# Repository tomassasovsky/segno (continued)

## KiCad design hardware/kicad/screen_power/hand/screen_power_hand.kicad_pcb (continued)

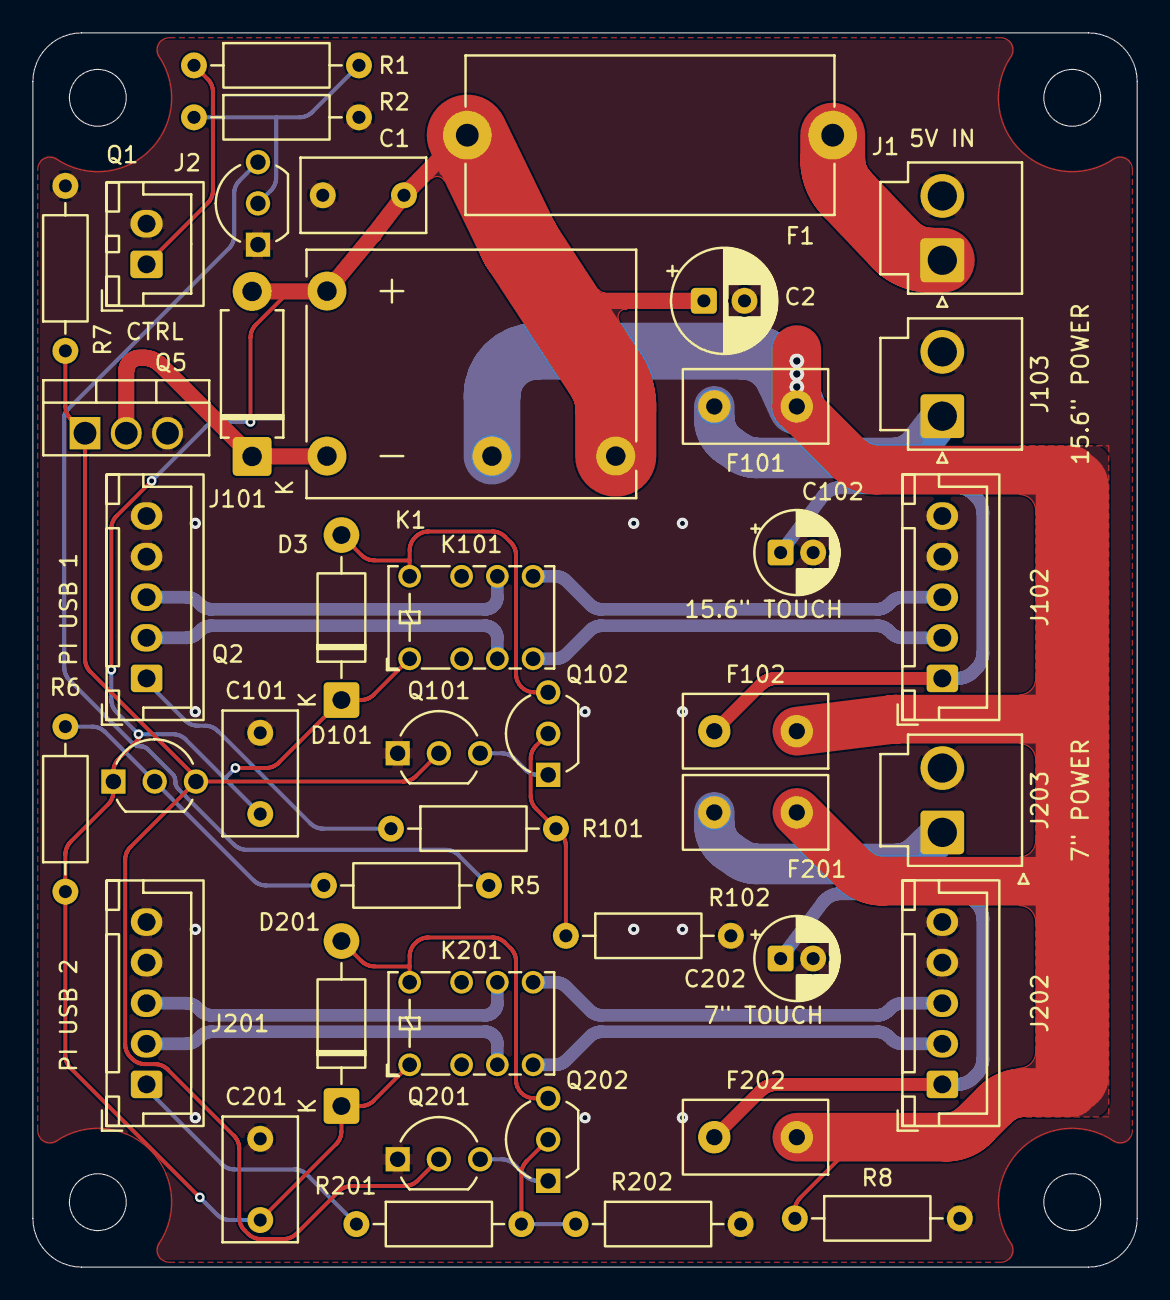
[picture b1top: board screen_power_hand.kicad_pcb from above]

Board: 2 copper layers, 68.0 x 76.0 mm, 46 parts (0 on the bottom side), 30 nets.

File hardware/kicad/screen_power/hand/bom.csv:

ref,value,footprint,mpn,group,quantity
J1,AUX 5V INPUT,Connector_JST:JST_VH_B2P-VH_1x02_P3.96mm_Vertical,B2P-VH(LF)(SN),Control,1
F1,8A time-lag,screen_power:Fuseholder_Schurter_OGN_0031.8201,0001.2513,Control,1
J2,GPIO17 / GND,Connector_JST:JST_XH_B2B-XH-A_1x02_P2.50mm_Vertical,B2B-XH-A(LF)(SN),Control,1
R1,1k 1%,Resistor_THT:R_Axial_DIN0207_L6.3mm_D2.5mm_P10.16mm_Horizontal,MFR-25FBF52-1K,Control,1
R2,4.7k 1%,Resistor_THT:R_Axial_DIN0207_L6.3mm_D2.5mm_P10.16mm_Horizontal,MFR-25FBF52-4K7,Control,1
Q1,2N3904,Package_TO_SOT_THT:TO-92_Inline_Wide,2N3904BU,Control,1
R5,5.6k 1%,Resistor_THT:R_Axial_DIN0207_L6.3mm_D2.5mm_P10.16mm_Horizontal,MFR-25FBF52-5K6,Control,1
R6,100k 1%,Resistor_THT:R_Axial_DIN0207_L6.3mm_D2.5mm_P10.16mm_Horizontal,MFR-25FBF52-100K,Control,1
R7,10k 1%,Resistor_THT:R_Axial_DIN0207_L6.3mm_D2.5mm_P10.16mm_Horizontal,MFR-25FBF52-10K,Control,1
Q2,2N3906,Package_TO_SOT_THT:TO-92_Inline_Wide,2N3906BU,Control,1
Q5,IRLZ44N,screen_power:TO-220-3_IRLZ44N,IRLZ44NPBF,Control,1
D3,P6KE6.8CA,Diode_THT:D_DO-15_P10.16mm_Horizontal,P6KE6.8CA,Control,1
K1,G6C-1117P-US,screen_power:Relay_Omron_G6C-1117P-US,G6C-1117P-US DC5,Control,1
R8,100R 1W 1%,Resistor_THT:R_Axial_DIN0207_L6.3mm_D2.5mm_P10.16mm_Horizontal,PR01000101000FA100,Control,1
C1,100nF 50V X7R,Capacitor_THT:C_Disc_D7.5mm_W4.4mm_P5.00mm,K104K10X7RF53H5,Control,1
C2,220uF 10V,Capacitor_THT:CP_Radial_D6.3mm_P2.50mm,EEU-FR1A221,Control,1
J101,PI USB / XH5,Connector_JST:JST_XH_B5B-XH-A_1x05_P2.50mm_Vertical,B5B-XH-A(LF)(SN),Screen 1,1
J102,TOUCH / XH5,Connector_JST:JST_XH_B5B-XH-A_1x05_P2.50mm_Vertical,B5B-XH-A(LF)(SN),Screen 1,1
J103,SCREEN 1 POWER,Connector_JST:JST_VH_B2P-VH_1x02_P3.96mm_Vertical,B2P-VH(LF)(SN),Screen 1,1
F101,4A time-lag,screen_power:Fuse_Bel_0697H_P5.08mm,0697H4000-02,Screen 1,1
F102,800mA time-lag,screen_power:Fuse_Bel_0697H_P5.08mm,0697H0800-02,Screen 1,1
K101,IM02TS,screen_power:Relay_DPDT_AXICOM_IMSeries_Pitch5.08mm_D0.90mm,1-1462037-3,Screen 1,1
Q101,TN0702,Package_TO_SOT_THT:TO-92_Inline_Wide,TN0702N3-G,Screen 1,1
Q102,TN0702,Package_TO_SOT_THT:TO-92_Inline_Wide,TN0702N3-G,Screen 1,1
R101,10k 1%,Resistor_THT:R_Axial_DIN0207_L6.3mm_D2.5mm_P10.16mm_Horizontal,MFR-25FBF52-10K,Screen 1,1
R102,100k 1%,Resistor_THT:R_Axial_DIN0207_L6.3mm_D2.5mm_P10.16mm_Horizontal,MFR-25FBF52-100K,Screen 1,1
D101,1N4007,Diode_THT:D_DO-41_SOD81_P10.16mm_Horizontal,1N4007G,Screen 1,1
C101,100nF 50V X7R,Capacitor_THT:C_Disc_D7.5mm_W4.4mm_P5.00mm,K104K10X7RF53H5,Screen 1,1
C102,150uF 10V,Capacitor_THT:CP_Radial_D5.0mm_P2.00mm,EEU-FR1A151,Screen 1,1
J201,PI USB / XH5,Connector_JST:JST_XH_B5B-XH-A_1x05_P2.50mm_Vertical,B5B-XH-A(LF)(SN),Screen 2,1
J202,TOUCH / XH5,Connector_JST:JST_XH_B5B-XH-A_1x05_P2.50mm_Vertical,B5B-XH-A(LF)(SN),Screen 2,1
J203,SCREEN 2 POWER,Connector_JST:JST_VH_B2P-VH_1x02_P3.96mm_Vertical,B2P-VH(LF)(SN),Screen 2,1
F201,4A time-lag,screen_power:Fuse_Bel_0697H_P5.08mm,0697H4000-02,Screen 2,1
F202,800mA time-lag,screen_power:Fuse_Bel_0697H_P5.08mm,0697H0800-02,Screen 2,1
K201,IM02TS,screen_power:Relay_DPDT_AXICOM_IMSeries_Pitch5.08mm_D0.90mm,1-1462037-3,Screen 2,1
Q201,TN0702,Package_TO_SOT_THT:TO-92_Inline_Wide,TN0702N3-G,Screen 2,1
Q202,TN0702,Package_TO_SOT_THT:TO-92_Inline_Wide,TN0702N3-G,Screen 2,1
R201,10k 1%,Resistor_THT:R_Axial_DIN0207_L6.3mm_D2.5mm_P10.16mm_Horizontal,MFR-25FBF52-10K,Screen 2,1
R202,100k 1%,Resistor_THT:R_Axial_DIN0207_L6.3mm_D2.5mm_P10.16mm_Horizontal,MFR-25FBF52-100K,Screen 2,1
D201,1N4007,Diode_THT:D_DO-41_SOD81_P10.16mm_Horizontal,1N4007G,Screen 2,1
C201,100nF 50V X7R,Capacitor_THT:C_Disc_D7.5mm_W4.4mm_P5.00mm,K104K10X7RF53H5,Screen 2,1
C202,150uF 10V,Capacitor_THT:CP_Radial_D5.0mm_P2.00mm,EEU-FR1A151,Screen 2,1
H1,M3,MountingHole:MountingHole_3.5mm,NPTH,Mechanical,1
H2,M3,MountingHole:MountingHole_3.5mm,NPTH,Mechanical,1
H3,M3,MountingHole:MountingHole_3.5mm,NPTH,Mechanical,1
H4,M3,MountingHole:MountingHole_3.5mm,NPTH,Mechanical,1
F1_HOLDER,5x20 input fuse holder,screen_power:Fuseholder_Schurter_OGN_0031.8201,0031.8201,Fuse holders,1

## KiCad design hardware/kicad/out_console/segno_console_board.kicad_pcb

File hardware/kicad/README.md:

<!-- cspell:words Omron -->
# Board generators

<!-- cspell:words XHP SXH -->

SKiDL scripts that emit KiCad netlists. One per board:

| script | board |
|---|---|
| `ring_board.py` | encoder + LED ring + XIAO RP2350, behind the faceplate (4-way link, #987) |
| `console_board.py` | console v3.1 — Pico 2 on the Pi's GPIO (#747); v3 adds the 4-way ring link (#987) and the CTRL ring sense; v3.1 moves MODE from GP5 to GP12 (#1388) |

The ring carrier now uses **white solder mask and black silkscreen** for LED
reflections. See [ring order and assembly notes](RING_ASSEMBLY.md) for the
September 24 hole allowances, order settings and USB programming connection.

Current console CTRL headers J20/J21 connect T / R / S / **RN** to the
Neutrik NJ6FD-V jacks; pin 4 uses ring-normal, leaving tip-normal and
sleeve-normal open. This keeps the presence pull-down off the ADC tip.
R11/R12 use the console Pico's `+3V3_PICO` supply so the AUX-powered ring
UART remains biased high while the Pi is off. See the
[connector wiring](../segno_wiring.md).

## Console connection to the screen-power board

**Revision P** removes two obsolete ground-fill exclusions beside screen-board
mounting hole H1. It retains all routes, pads and placements and uses five-pin XH plugs for all four USB touch/data cable tails.
The fifth contact terminates each shield to PCB GND, so the whole cable
disconnects with one plug. The separate drain solder pads are removed, with
local placement changes for the longer headers. The Omron power relay,
replaceable 8 A input fuse, four soldered branch fuses, AUX-powered USB coils
and independent host detection remain. The board is still two layers and
68 × 76 mm. See the [screen design and wiring](screen_power/README.md).

Use the archives identified by the
[manufacturing record](../../docs/reviews/pcb-finish-all-three-1072/manufacturing-zips.json)
and its matching review evidence. Console copper is unchanged. The white
ring board retains its tracks, pads, rear ground and full-white capacity;
two small dead-end front-ground fingers have been removed. No pre-PCB prototype or additional
owner measurement is required by this change.

Use **J25**, the two-pin through-hole JST XH connector beside the Pi ribbon
connector. It is already included in the console source, routed PCB and BOM
under #1072. The top-side label reads `SCREEN`; the pin map is documented below.
PD J23, RING J6, screen-control J25 and PI PWR J9 share the same horizontal
connector row. J9 sits immediately beside the Pi ribbon connector; it carries
the floating power-button pair, not a supply rail. PWR BTN J8 remains on the
rear-panel connector row.

| Console J25 | Screen-power J2 | Signal |
| --- | --- | --- |
| Pin 1 | Pin 1 | BCM GPIO17, from Pi ribbon J2 physical pin 11 |
| Pin 2 | Pin 2 | Ground |

The connector is JST **B2B-XH-A(LF)(SN)**, 2.50 mm pitch. Use one short
two-wire 22 AWG cable with an XHP-2 housing and two SXH-001T-P0.6 contacts at
each end. Check numbered pin continuity before connecting it; cable colors
and mirrored views do not establish polarity.

The existing Pi-to-console ribbon remains direct. The dedicated AUX buck
feeds screen-power J1 separately; no screen load passes through console J3
or J25. No extra USB or power connector is needed on the console for this
interface. See the [screen-board wiring](screen_power/README.md) and
[console connector verification](../../docs/reviews/console-screen-connector-1072/verification.md).
The latest [placement verification](../../docs/reviews/console-pi-power-placement-1072/verification.md)
covers the PI PWR move and retained PD alignment. The subsequent
[top-label verification](../../docs/reviews/console-screen-label-1072/verification.md)
covers the `SCREEN` text change and current exports.

The screen planning load is **4.25 A shared**, including both main outputs,
both touch outputs. Add 60 mA for the bleeder and 150 mA for coils/control,
for a **4.46 A** screen-board input allowance. The old 6 A expansion allowance is
retired. The 3 A main and 500 mA touch lead ceilings are not additive or
simultaneous guarantees. The selected 35-pixel ring uses a separate direct
AUX branch and does not pass through console power copper or the screen-power relay. See the
[screen-board assessment](screen_power/README.md#circuit-and-limits).

The ring's power is budgeted for **40 LEDs at unrestricted full white**, five
more than the 35 fitted. Follow the
[ring assembly guide](RING_ASSEMBLY.md): console J6 pins 3/4 carry UART only,
with cavities 1/2 empty. Supply strip power and ring J1 pins 1/2 from separate
short pairs at the near-ring AUX split; ring J2 pin 3 carries DIN only, with
pins 1/2/4 unconnected. The budget is 2.4 A for LED channels, 40 mA idle and
200 mA for the ring controller. The retained console/carrier power routes do
not replace this harness's voltage-margin requirement. Genuine XH contacts
use 22 AWG pigtails; do not crimp the 16 AWG trunk into them.
Use one external strip, or one direct-mount 24/16-LED module. A second ring is
outside this budget. See the [JST rating](https://www.jst-mfg.com/product/pdf/eng/eXH.pdf).

## Running them

```bash
python3.12 -m venv .venv && ./.venv/bin/pip install -r requirements.txt
cd hardware/kicad && ./.venv/bin/python console_board.py
```

**Run from `hardware/kicad/`.** `generate_netlist()` writes `<script>.net` into the
current working directory, so running from the repo root silently drops the netlist
in the wrong place while reporting success.

The routing pipelines finish unlocked signal bends with `round_routes.py`
after setting trace widths and before refilling copper. It uses KiCad's native
pad and track geometry to preserve connections and clearance. Locked power
routes and the screen's paired USB traces are rounded by their own generators.
Run `test_round_routes.py` with KiCad's Python to exercise the native contact,
keepout, small-radius and repeat-run regression cases without changing a board.

## Two things that will mislead you

**A netlist diff is not a design change.** SKiDL assigns a *random* `SKiDL Tag` to
every `Part` without an explicit `tag=`, and component `tstamps` derive from it. Two
runs of the **same** version on unchanged source differ by ~190 lines — all tags,
timestamps and the tool version string, with **zero** net changes. Pinning skidl does
not fix this. Judge a run by `0 errors found while running ERC` and the `(net ...)`
blocks, not by `git diff`.

**Prefer upstream footprints.** `segno.pretty/` exists for parts KiCad does not ship
(the NeoPixel Ring 24, the Same Sky ACZ11BR1E-20FD1-20C encoder, the module mount-pad and wire-pad
helpers). It is not a place to re-draw something that already exists. The Pico 2, for instance, is KiCad's own
`Module:RaspberryPi_Pico_Common_THT` — its description explicitly says it supports
Pico 2, and it is maintained upstream.

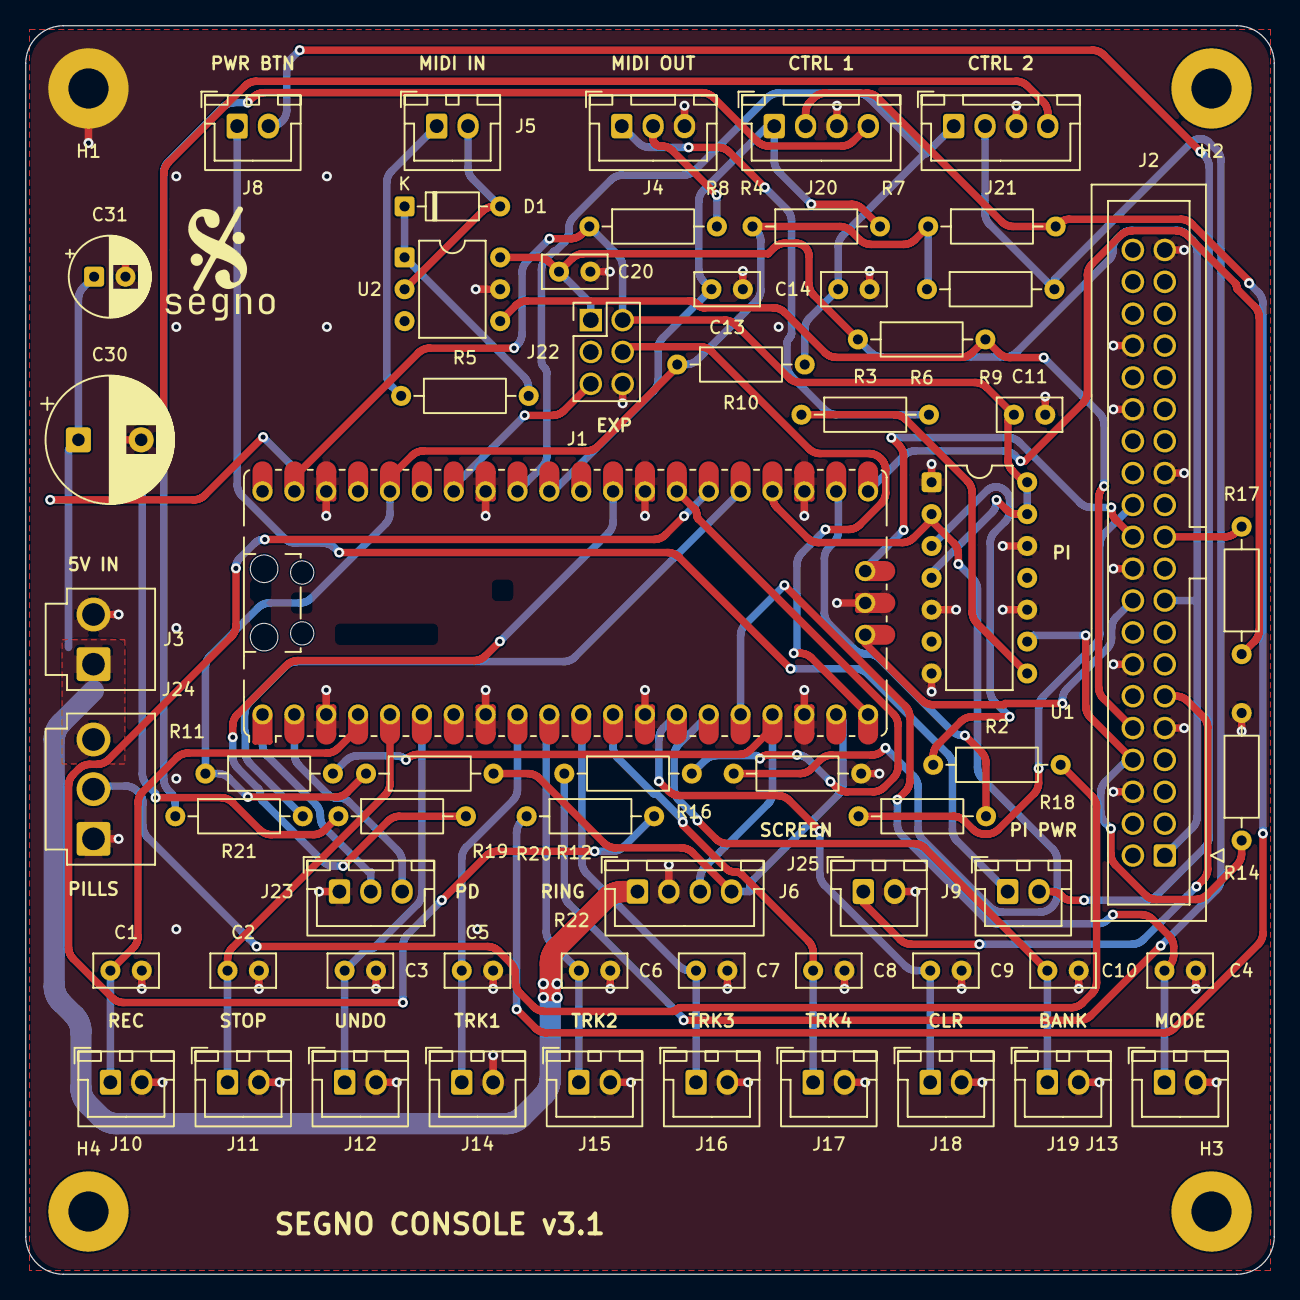
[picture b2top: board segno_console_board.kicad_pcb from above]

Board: 2 copper layers, 99.5 x 99.5 mm, 66 parts (0 on the bottom side), 50 nets.

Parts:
C1, C2, C3, C4, C5, C6, C7, C8, C9, C10, C11, C13, C14, C20: C_Disc_D5.0mm_W2.5mm_P2.50mm
C30: CP_Radial_D10.0mm_P5.00mm
C31: CP_Radial_D6.3mm_P2.50mm
D1: D_DO-35_SOD27_P7.62mm_Horizontal
H1, H2, H3, H4: MountingHole_3.2mm_M3_Pad
J1: RaspberryPi_Pico_SMD_HandSolder; RaspberryPi_Pico_SMD_or_THT_Debug
J2: IDC-Header_2x20_P2.54mm_Vertical
J3: JST_VH_B2P-VH_1x02_P3.96mm_Vertical
J4, J23: JST_XH_B3B-XH-A_1x03_P2.50mm_Vertical
J5, J8, J9, J10, J11, J12, J13, J14, J15, J16, J17, J18, J19, J25: JST_XH_B2B-XH-A_1x02_P2.50mm_Vertical
J6, J20, J21: JST_XH_B4B-XH-A_1x04_P2.50mm_Vertical
J22: PinHeader_2x03_P2.54mm_Vertical
J24: JST_VH_B3P-VH_1x03_P3.96mm_Vertical
R2, R3, R4, R5, R6, R7, R8, R9, R10, R11, R12, R14, R16, R17, R19, R20, R21, R22: R_Axial_DIN0207_L6.3mm_D2.5mm_P10.16mm_Horizontal
R18: 6.8k; R_Axial_DIN0207_L6.3mm_D2.5mm_P10.16mm_Horizontal
U1: DIP-14_W7.62mm
U2: DIP-6_W7.62mm

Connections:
+3V3: C20.1, J2.1, J2.17, J22.1, R6.1, U2.6
+3V3_PICO: J1.36, R7.1, R8.1, R9.1, R10.1, R11.1, R12.1
+5V: C11.1, C30.1, C31.1, J1.39, J3.1, J6.1, J22.2, J24.3, R4.1, U1.4, U1.13, U1.14
CTRL1_PRESENT: J1.25, R21.2
CTRL1_RING: J1.26, R19.2
CTRL1_TIP: C13.1, J1.31, J20.1, R8.2
CTRL2_PRESENT: J1.29, R22.2
CTRL2_RING: J1.27, R20.2
CTRL2_TIP: C14.1, J1.32, J21.1, R10.2
EXP_GP15: J1.20, J22.4
EXP_GP28: J1.34, J22.5
GND: C1.2, C2.2, C3.2, C4.2, C5.2, C6.2, C7.2, C8.2, C9.2, C10.2, C11.2, C13.2, C14.2, C20.2, C30.2, C31.2, H1.1, J1.3, J1.8, J1.13, J1.18, J1.23, J1.28, J1.33, J1.38, J1.D2, J2.6, J2.9, J2.14, J2.20, J2.25, J2.30, J2.34, J2.39, J3.2, J4.3, J6.2, J10.2, J11.2, J12.2, J13.2, J14.2, J15.2, J16.2, J17.2, J18.2, J19.2, J20.3, J21.3, J22.6, J23.1, J24.1, J25.2, R14.2, R16.2, U1.1, U1.5, U1.7, U1.10, U1.12, U2.5
IND_DATA: J1.24, R16.1, U1.2
IND_DATA_BUF: R2.1, U1.3
IND_DATA_OUT: J24.2, R2.2
J20_REF: J20.2, R7.2, R19.1
J20_RN: J20.4, R21.1
J21_REF: J21.2, R9.2, R20.1
J21_RN: J21.4, R22.1
LINK_RX: J1.22, R18.2
LINK_RX_PI: J2.24, R18.1
LINK_TO_CONSOLE: J1.19, J6.4, R12.2
LINK_TO_RING: J1.17, J6.3, R11.2
LINK_TX: J1.21, R17.1
LINK_TX_PI: J2.21, R17.2
MIDI_OUT_BUF: R3.1, U1.8
MIDI_RX: J2.10, R6.2, U2.4
MIDI_TX: J2.8, R14.1, U1.9
unnamed: J4.1, R3.2
unnamed: J4.2, R4.2
unnamed: J5.1, R5.1
unnamed: D1.1, R5.2, U2.1
unnamed: D1.2, J5.2, U2.2
PD_SCL: J1.2, J23.3
PD_SDA: J1.1, J23.2
PI_GPIO17: J2.11, J25.1
PWR_BTN: J8.1, J9.1
PWR_BTN_RET: J8.2, J9.2
SWCLK: J1.D1, J2.18
SWDIO: J1.D3, J2.22
SW_BANK: C10.1, J1.15, J19.1
SW_CLEAR: C9.1, J1.14, J18.1
SW_MODE: C4.1, J1.16, J13.1
SW_RECPLAY: C1.1, J1.4, J10.1
SW_STOP: C2.1, J1.5, J11.1
SW_TRACK1: C5.1, J1.9, J14.1
SW_TRACK2: C6.1, J1.10, J15.1
SW_TRACK3: C7.1, J1.11, J16.1
SW_TRACK4: C8.1, J1.12, J17.1
SW_UNDO: C3.1, J1.6, J12.1

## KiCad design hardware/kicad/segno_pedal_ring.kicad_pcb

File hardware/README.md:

# Hardware

The physical parts of the Segno floor console: the printed circuit boards, the
sheet-metal enclosure, the printed parts that sit inside it, the decals, and
the documents that describe how to buy, build and wire one unit.

Most of this folder is generated. Python scripts produce the KiCad boards
(SKiDL for netlists, KiCad's own `pcbnew` Python module for layout) and the
mechanical parts (cadquery). Their outputs, STEP, DXF, PDF, STL and Gerber
archives, are committed next to them so that the files can be opened without
running anything. When a generator and its output disagree, the generator is
the source; regenerate rather than editing the output.

The firmware for the boards is in [`../firmware`](../firmware/README.md).

## Current design

The current console uses three boards and one enclosure revision. The
[manufacturing package](MANUFACTURING.md) is the reference for what to order:

| Part | Revision | Source |
| --- | --- | --- |
| Console board | v3, Pico 2 (RP2350) on the Pi's 40-pin header | [`kicad/console_board.py`](kicad/console_board.py), [`kicad/console_board_pcb.py`](kicad/console_board_pcb.py) |
| Ring carrier | XIAO RP2350, encoder and LED ring, white solder mask | [`kicad/ring_board.py`](kicad/ring_board.py), [`kicad/segno_pedal_ring.kicad_pcb`](kicad/segno_pedal_ring.kicad_pcb) |
| Screen power board | Revision P | [`kicad/screen_power/`](kicad/screen_power/README.md) |
| Enclosure | 2026-09-30 integrated revision | [`enclosure/segno_enclosure.py`](enclosure/segno_enclosure.py) |

The console board v2 is superseded by v3. Some documents written before the
change still call the console board "v2". The enclosure's fabrication release is
on hold pending the sheet-metal shop's tooling acceptance and a separate
structural assessment (#1019); [`enclosure/RELEASE_REVIEW.md`](enclosure/RELEASE_REVIEW.md)
lists the open items.

## Documents

| File | Contents |
| --- | --- |
| [`MANUFACTURING.md`](MANUFACTURING.md) | The manufacturing package for one console: the metal parts and their shops, 3D-printed parts, engraved pedal tiles, vinyl decals, PCBs, purchased parts and the screw and insert schedule. Start here to build or order anything. |
| [`segno_wiring.md`](segno_wiring.md) | System wiring: the block diagram, the 20 V USB-C power input and its two 5 V converters, the console board's internal cables, the Raspberry Pi connections, the rear panel and grounding. |
| [`segno_console_shopping_list.md`](segno_console_shopping_list.md) | Per-console bill of materials with local (Argentina) sourcing notes: compute and displays, audio, foot controls, LEDs, power, boards and mechanical parts. |
| [`segno_enclosure_design.md`](segno_enclosure_design.md) | Design notes for the sheet-metal enclosure: overall geometry, pedal platforms, faceplate layout, rear I/O, internal mounting, material, and the generator's assertion checks. |
| [`segno_console_board_v2_soldering_guide.md`](segno_console_board_v2_soldering_guide.md) | Hand-assembly guide for the console board v2, with [an illustration](segno_console_board_v2_soldering_guide.png). The v2-specific parts are historical; for the v3 boards use [`v3_soldering`](v3_soldering/README.md). |

## Folders

### [`kicad`](kicad/README.md)

The board sources. SKiDL scripts emit the netlists (`console_board.py`,
`ring_board.py`), and `pcbnew` scripts place, route and check the boards.
`segno.pretty/` holds the few footprints KiCad does not ship.
[`RING_ASSEMBLY.md`](kicad/RING_ASSEMBLY.md) and
[`RING_ENCODER.md`](kicad/RING_ENCODER.md) cover the ring carrier's assembly,
order settings and encoder fit. `screen_power/` is the screen power and touch
switch board, a self-contained KiCad project with its own build script.
`fab/` holds the Gerber archives and BOMs that were sent to the board
manufacturer, including earlier screen-power revisions; `out_console/` and
`out_ring/` hold the generated boards and Gerbers. Open the `.kicad_pcb` and
`.kicad_pro` files with KiCad.

### [`v3_soldering`](v3_soldering/README.md)

Solder order for the three current boards (console v3, ring carrier, screen
power Revision P): parts lists, numbered solder-order images and KiCad 3D
renders. `tools/build.sh` regenerates the images from the KiCad boards.

### `enclosure`

The parametric enclosure generator, `segno_enclosure.py` (cadquery). It runs a
set of geometry assertions, then writes STEP, DXF and PDF drawings and STL
print files to `out/`, and assembles the vendor archives. `tests/` holds the
enclosure tests. `formed/` holds the folded parts exported from the Fusion 360
model by `fusion_export_formed.py`, which the generator checks its flat
patterns against. `fusion/Segno_console_populated.f3d` is the populated Fusion
360 assembly. The Markdown files in this folder are working records:

- [`RELEASE_REVIEW.md`](enclosure/RELEASE_REVIEW.md): the evidence and open
  items for the current manufacturing release.
- [`SHOP_REVIEW.md`](enclosure/SHOP_REVIEW.md): internal supplier notes and
  draft messages; nothing in it has been sent.
- [`FUSION_MODELS.md`](enclosure/FUSION_MODELS.md): a dated log of changes to
  the Fusion 360 documents and how to edit them safely.
- [`HANDOFF_1019.md`](enclosure/HANDOFF_1019.md): a point-in-time handoff on
  the enclosure's load and stomp analysis (#1019).

The underscore-prefixed scripts are one-off checks and fit-test jigs, such as
the stomp finite-element runs and the print checks.

### `strip_ring`

`console_ring.py` (cadquery) generates the printed parts of the LED strip ring
that sits under the faceplate around the encoder: the diffuser, the cup that
carries the strip, the encoder retainer, spacer and centre cap, and a bench
faceplate. Outputs are STEP and STL in `out_console/`;
`test_console_ring.py` checks the geometry.

### [`pill_light_mask`](pill_light_mask/README.md)

The housings for the faceplate's indicator pills, each lit by an eight-LED
strip segment: a carrier, a white lens and mounting parts, generated with cadquery as
STEP and STL. [`PLATFORM_MOUNT.md`](pill_light_mask/PLATFORM_MOUNT.md)
describes the friction-fit housing for the printed pedal platforms.
`simulator.html` is a browser preview of the pill animation.

### `decals`

`decals.py` generates the two transfer-cut vinyl decals, the lid logo and the
rear connector labels, as DXF, SVG and PDF at 1:1, plus a cut sheet and
placement templates. `test_decals.py` checks them. Outputs are in `out/`.

### [`console`](console/README.md)

Notes on the console as a whole: power, thermals and how the enclosure, the
board and the Pi fit together. `stusb4500_pdo/` is an Arduino sketch, run from
an Arduino UNO, that reprograms the USB-C power-delivery trigger board when
the console board cannot reach it.

### [`bench`](bench/README.md)

Hardware bench tests that CI cannot run. `midi_din_test.py` runs on the
appliance and checks that the console board's two DIN MIDI sockets carry
exact bytes in both directions.

### [`switch_mount`](switch_mount/README.md)

A printed platform that holds a silent switch inside a Cherub WTB-006
footswitch. It is drawn by hand in Fusion 360; the folder holds its STEP and
STL exports.

### [`ring_diffuser`](ring_diffuser/README.md)

A snap-on diffuser for a 16-pixel NeoPixel ring, used on the bench before the
faceplate existed. Generated by `ring16_diffuser.py` (cadquery). It is not the
console's ring window and does not fit the current ring carrier.

### [`led_strip`](led_strip/README.md)

A single-LED WS2812B indicator board, generated with `pcbnew`. It is not used
by the console, which uses segments cut from a bare LED strip instead; the
design is kept because it is complete.

## License

The hardware designs are covered by the repository's
[GPL-3.0-or-later license](../LICENSE). Two files under
`kicad/screen_power/` carry third-party terms for material copied from the
KiCad libraries: [`LIBRARY_LICENSE.txt`](kicad/screen_power/LIBRARY_LICENSE.txt)
(CC-BY-SA 4.0 with KiCad's exception for designs that use the libraries) and
the 3D-model credits in [`models/licenses/`](kicad/screen_power/models/licenses/).

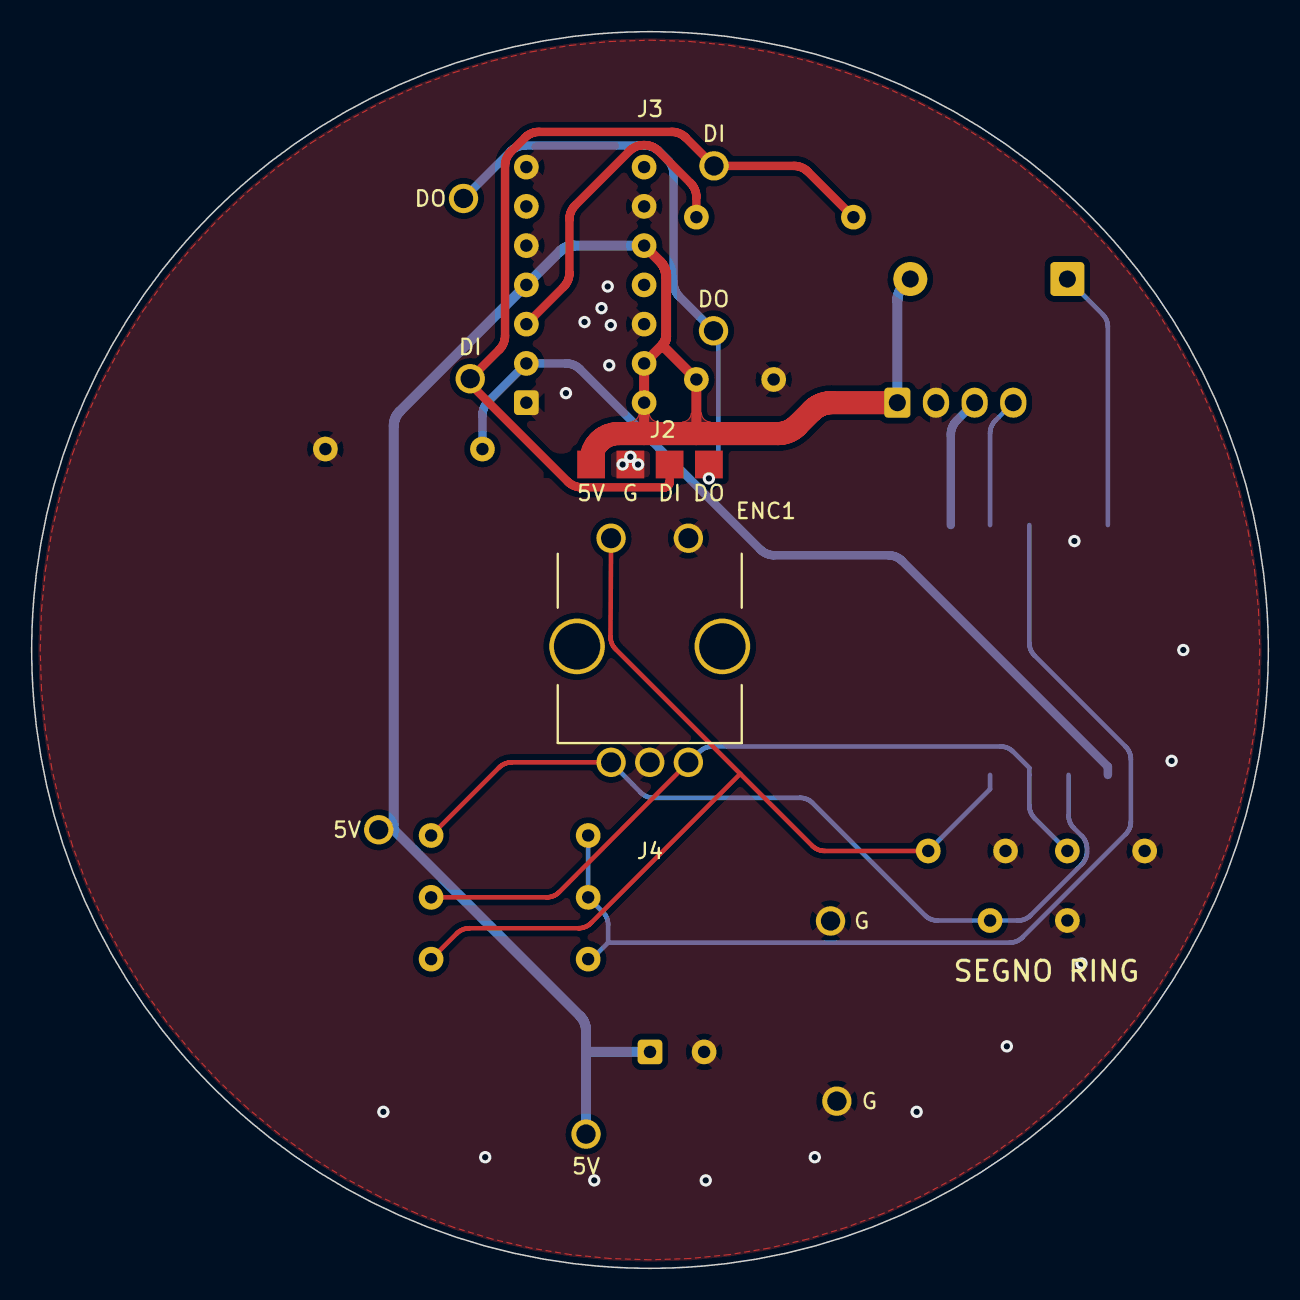
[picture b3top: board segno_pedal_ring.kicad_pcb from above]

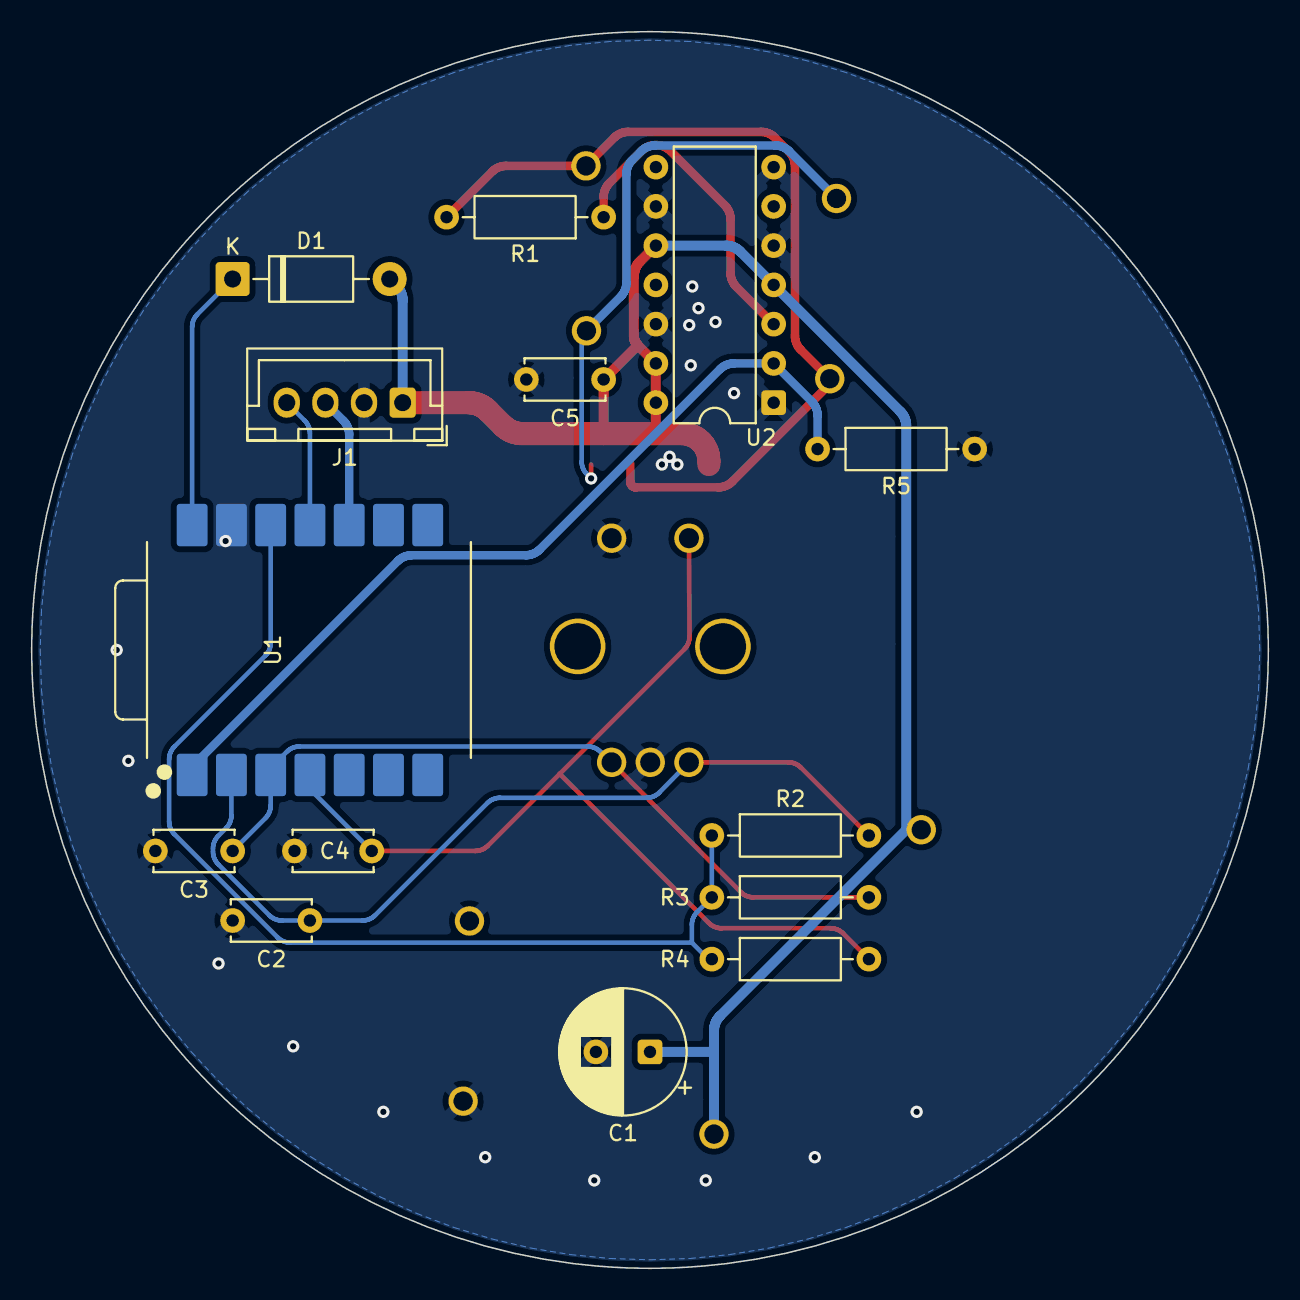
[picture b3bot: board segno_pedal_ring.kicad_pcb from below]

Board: 2 copper layers, 80.0 x 80.0 mm, 19 parts (14 on the bottom side), 13 nets.

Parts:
C1: 470uF 16V low-ESR <=0.15R; CP_Radial_D8.0mm_P3.50mm
C2, C3, C4: 10nF; C_Disc_D5.0mm_W2.5mm_P5.00mm
C5: 100nF; C_Disc_D5.0mm_W2.5mm_P5.00mm
D1: 1N5819; D_DO-41_SOD81_P10.16mm_Horizontal
ENC1: ACZ11BR1E-20FD1-20C; RotaryEncoder_SameSky_ACZ11BR1E-20FD1-20C
J1: Conn_01x04; JST_XH_B4B-XH-A_1x04_P2.50mm_Vertical
J2: NEOPIXEL; WirePads_1x04
J3: RINGPINS24; ModuleMountPads_Ring24
J4: RINGPINS16; ModuleMountPads_4
R1: 330; R_Axial_DIN0207_L6.3mm_D2.5mm_P10.16mm_Horizontal
R2, R3, R4: 10k; R_Axial_DIN0207_L6.3mm_D2.5mm_P10.16mm_Horizontal
R5: 100k; R_Axial_DIN0207_L6.3mm_D2.5mm_P10.16mm_Horizontal
RING1: NeoPixel24; NeoPixel_Ring24
U1: XIAO-RP2350; XIAO_RP2350_SMD
U2: 74AHCT125N; DIP-14_W7.62mm

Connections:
+3V3: R2.1, R3.1, R4.1, U1.12
+5V_LED: C1.1, C5.1, D1.2, J1.1, J2.1, J3.2, J4.2, U2.4, U2.10, U2.13, U2.14
+5V_MCU: D1.1, U1.14
ENC_A: C2.1, ENC1.A, R2.2, U1.2
ENC_B: C3.1, ENC1.B, R3.2, U1.3
ENC_SW: C4.1, ENC1.S1, R4.2, U1.4
GND: C1.2, C2.2, C3.2, C4.2, C5.2, ENC1.C, ENC1.S2, J1.2, J2.2, J3.3, J4.3, R5.2, U1.13, U2.1, U2.5, U2.7, U2.9, U2.12
LINK_TO_CONSOLE: J1.4, U1.11
LINK_TO_RING: J1.3, U1.10
RING_DATA: J2.3, J3.1, J4.1, R1.2
RING_DATA_3V3: R5.1, U1.1, U2.2
RING_DATA_5V: R1.1, U2.3
RING_DOUT: J2.4, J3.4, J4.4

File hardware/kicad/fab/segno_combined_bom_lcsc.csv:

LCSC,Comment,Value,Package,Qty,Designator,Notes
,Ceramic capacitor,10nF 50V X7R +/-10%,C_Disc_D5.0mm_P5.00mm (THT),3,"RING:C2,C3,C4","Vishay K103K10X7RF53H5: 5mm pitch, 3.6x2.3mm body, 0.5mm leads; encoder release filters. See RING_ENCODER.md."
,Ceramic capacitor,100nF,C_Disc_D5.0mm_P5.00mm (THT),1,RING:C5,U2 supply decoupling only; do not substitute the 10nF encoder-filter value.
,Electrolytic,470uF 16V low-ESR <=0.15R,CP_Radial_D8.0mm_P3.50mm,1,RING:C1,Low-ESR grade (e.g. Panasonic FC / Nichicon PW) -- GP parts in the same can run ~0.5R and ripple the LED rail
,Resistor,330R,Axial 1/4W DIN0207,1,RING:R1,WS2812 data series resistor. Any in-stock 1/4W axial
,Resistor,10k,Axial 1/4W DIN0207,3,"RING:R2,R3,R4",Encoder pull-ups to the XIAO's 3V3_OUT. Any in-stock 1/4W axial
,Resistor,100k,Axial 1/4W DIN0207,1,RING:R5,Holds the level shifter input low while the XIAO is not driving it. Any in-stock 1/4W axial
,Schottky diode,1N5819,DO-41,1,RING:D1,Series diode into the XIAO's VBUS pad (band = cathode toward the module)
C354152,74AHCT125N,74AHCT125N,DIP-14,1,RING:U2,TI SN74AHCT125N quad buffer (3V3 -> 5V for the ring data)
,Seeed Studio XIAO RP2350,XIAO RP2350,Castellated module 21x17.8mm,1,RING:U1,"Not an LCSC part -- Seeed, DigiKey or Mouser. Soldered by its 14 side pads; its underside pads stay unsoldered (a square of Kapton under it is cheap insurance)"
,Rotary encoder,ACZ11BR1E-20FD1-20C,RotaryEncoder_SameSky_ACZ11BR1E-20FD1-20C,1,RING:ENC1,Same Sky exact part; DigiKey 102-1768-ND; vertical switch 20mm D-shaft M7x0.75 H5; 20 pulses/20 detents; hand solder <=350C <=3s; see RING_ENCODER.md
,Encoder mounting nut,SJ5-43502PM-nut,M7x0.75 2.0mm thick 10mm AF,1,RING:ENC1 hardware,Same Sky separately sourced; clamp 2mm disc without washer; exact drawing and stack in RING_ENCODER.md
C144395,JST B4B-XH-A,4P 2.5mm,JST_XH vertical,1,RING:J1,Selected 40-strip harness: pins 1/2 to near-ring AUX split via own 50 mm 22 AWG pair; pins 3/4 to console J6 pins 3/4; console J6 cavities 1/2 empty. Buy XHP-4 housings and SXH-001T-P0.6 contacts.
,External WS2812B strip,40 LEDs at 5 V,Existing strip in its separate housing,1,RING:J2,Selected assembly: J2 pin 3 DIN only; pins 1/2/4 unused. Strip power goes directly to near-ring AUX split. J3/J4 empty. Reuse existing 40-LED strip; see RING_ASSEMBLY.md for required 16 AWG trunk/22 AWG branches.
,Strip-entry bulk capacitor,1000uF 10V Panasonic EEUFR1A102,Radial 10x16mm P5mm; external harness,1,RING:strip harness,Positive to strip +5V; striped negative to strip GND at power entry. Short leads; separately sleeve joints and secure body outside optics with vent clear. Separate from carrier C1.

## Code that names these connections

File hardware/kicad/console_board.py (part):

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link_rx = Net("LINK_RX")   # Pi   -> Pico (3V3 both ends)
link_tx_pi = Net("LINK_TX_PI")   # ...but series R17/R18: these are the
link_rx_pi = Net("LINK_RX_PI")   # two nets that cross power domains -- see below
pi_gpio17 = Net("PI_GPIO17")  # screen-power daughterboard enable, 3.3 V only
midi_tx = Net("MIDI_TX")   # Pi uart0 TX -> AHCT125 -> DIN OUT
midi_rx = Net("MIDI_RX")   # opto (3V3) -> Pi uart0 RX
midi_out_buf = Net("MIDI_OUT_BUF")
pwr_btn = Net("PWR_BTN")   # rear button -> the Pi's own PWR pads, NOT a GPIO
# The button's other contact, carried through to the Pi's other pad. NOT GND (#1062):
# see J9.
pwr_btn_ret = Net("PWR_BTN_RET")
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# the power inlet are on anyway.
#
# GP5 is the one exception, and it is a routing call rather than an oversight.
# GP12 left J22 for SW_MODE (#1388, see the pin map below), and GP5, the pin MODE
# vacated, cannot follow it onto J22: no 0.6 mm track fits between two of the
# module's through-holes at 2.54 mm pitch, so pad 7 reaches J22 only by going
# round the module's LEFT end, through the J3/J24 power bar and the CTRL and
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FSW_ORDER = ["RECPLAY", "STOP", "UNDO", "MODE", "TRACK1",
             "TRACK2", "TRACK3", "TRACK4", "CLEAR", "BANK"]

pico[PICO[GPIO["LINK_TX"]]] += link_tx
pico[PICO[GPIO["LINK_RX"]]] += link_rx
pico[PICO[GPIO["IND_DATA"]]] += ind_data
pico[PICO[GPIO["LINK_TO_RING"]]] += link_to_ring
pico[PICO[GPIO["LINK_TO_CONSOLE"]]] += link_to_console
pico[PICO[GPIO["CTRL1_TIP"]]] += ctrl1
pico[PICO[GPIO["CTRL2_TIP"]]] += ctrl2
ctrl1_ring = Net("CTRL1_RING")
ctrl2_ring = Net("CTRL2_RING")
pico[PICO[GPIO["CTRL1_RING"]]] += ctrl1_ring
pico[PICO[GPIO["CTRL2_RING"]]] += ctrl2_ring
pd_sda, pd_scl = Net("PD_SDA"), Net("PD_SCL")
pico[PICO[GPIO["PD_SDA"]]] += pd_sda
pico[PICO[GPIO["PD_SCL"]]] += pd_scl
ctrl1_present, ctrl2_present = Net("CTRL1_PRESENT"), Net("CTRL2_PRESENT")
pico[PICO[GPIO["CTRL1_PRESENT"]]] += ctrl1_present
pico[PICO[GPIO["CTRL2_PRESENT"]]] += ctrl2_present

# ---- J10..J19: footswitches -- clamp, 1k series, 100nF debounce, one JST each -
sw_nets = {}       # name -> the Pico side: GPIO, debounce cap, resistor
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
# ---- J4/J5: DIN-5 MIDI, terminating on the PI's uart0 -----------------------
j_mout = jst(3, "J4", "MIDI_OUT")
R("220", ref="R3")[1, 2] += midi_out_buf, j_mout[1]      # DIN pin 5
R("220", ref="R4")[1, 2] += v5, j_mout[2]                # DIN pin 4
j_mout[3] += gnd                               # DIN pin 2 (shield) -- OUT only

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# ---- J22: expansion -- the three GPIO that are otherwise doing nothing ------
# Deliberately unpopulated by default. GP28 is an ADC, so it can carry a third
# pedal input; GP15 is a plain digital pin. Nothing on the board depends on it.
# Pin 3 is unconnected since GP12 became SW_MODE (#1388; why GP5 does not take
# it is under SPARE_GPIO). The GPIO pins keep their v3 positions, so the header
# and its copper are otherwise unchanged; on a reworked v3 board pin 3 carries
# MODE, which is why it is not reused for anything else.
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    1: v3v3, 17: v3v3,
    6: gnd, 9: gnd, 14: gnd, 20: gnd, 25: gnd, 30: gnd, 34: gnd, 39: gnd,
    8: midi_tx, 10: midi_rx,
    11: pi_gpio17,  # GPIO17 enables the separate screen-power board
    # LINK sits MID-HEADER, on `dtoverlay=uart3-pi5` -- "Enable uart 3 on GPIOs 8-9.
    # Pi 5 only." Physical pins 24 and 21 are positions 11 and 12 of their rows, as
    # far from both ends as this header gets.
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    # GPIO8/9 are SPI0's CE0 and MISO. Nothing here uses SPI0: the screens are USB
    # and HDMI, the SSD is PCIe, and MIDI and the link are UARTs. If an SPI device
    # ever lands on this Pi, this is the pair it will want.
    24: link_rx_pi,  # GPIO8, uart3 TX -> R18 -> Pico RX  (3V3 -> 3V3, via 6.8 k)
    21: link_tx_pi,  # GPIO9, uart3 RX <- R17 <- Pico TX  (3V3 -> 3V3, via 10 k)
    18: swclk, 22: swdio,
}
j_pi = Part("Connector_Generic", "Conn_02x20_Odd_Even",
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# Control only: the daughterboard takes its power directly from BUCK_AUX.
# Its input series resistor and pull-down keep both screens off by default.
j_screen = jst(2, "J25", "SCREEN_ENABLE")
j_screen[1] += pi_gpio17
j_screen[2] += gnd

# ---- gates ------------------------------------------------------------------
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        used[gp] = "J22 expansion"
    # LINK must be a real hardware UART pair on ONE instance -- GP16 TX with GP29 RX
    # looks fine in a pin list and is two different UARTs.
    assert any(GPIO["LINK_TX"] in tx and GPIO["LINK_RX"] in rx
               for tx, rx in UART_PINS.values()), (
        f"LINK_UART: GP{GPIO['LINK_TX']}/GP{GPIO['LINK_RX']} is not a TX/RX pair on "
        f"one UART instance -- valid pairs are {UART_PINS}")

    # Check electrical limits, not just a remembered BOM value: increasing R18
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    assert _rx_ohms > 0 and 3.63 / (_rx_ohms * 0.99) <= 0.001, (
        "LINK_RX_DRIVE: R18 exceeds the retained 1 mA rail-difference fault bound")

    assert any(GPIO["PD_SDA"] in sda and GPIO["PD_SCL"] in scl
               for sda, scl in I2C_PINS.values()), (
        f"PD_I2C: GP{GPIO['PD_SDA']}/GP{GPIO['PD_SCL']} is not an SDA/SCL pair on "
        f"one I2C instance -- valid pairs are {I2C_PINS}")

    for name, gp in GPIO.items():
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    # the PMIC wakes them. A gate can enforce a wrong belief just as firmly as a
    # right one; this one did, for the whole design.
    assert 5 not in PI_HDR, (
        "PWR_BTN: Pi header pin 5 (GPIO3) cannot wake a Pi 5 -- the button belongs "
        "on the Pi's own J2 solder pads, brought out as J9")
    assert {n.name for n in j_pi_btn[1].nets} == {"PWR_BTN"}, (
        "PWR_BTN: J9 must carry the button through to the Pi's J2 pads")
    # ...as a floating pair: pin to pin with J8, and nothing else on either net.
    for _pin, _net in ((1, pwr_btn), (2, pwr_btn_ret)):
        _nodes = {(p.ref, str(pin.num)) for p in default_circuit.parts
                  for pin in p.pins if _net in pin.nets}
        assert _nodes == {("J8", str(_pin)), ("J9", str(_pin))}, (
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        "CTRL_SUPPLY: Pico 3V3 must not be tied to the Pi 3V3 rail")

    # ...and the buck must not be paralleled with the Pi's own 5 V rail.
    assert {(p.part.ref, str(p.num)) for p in pi_gpio17.get_pins()} == {
        ("J2", "11"), ("J25", "1")
    }, "SCREEN_ENABLE: GPIO17 must connect only Pi physical pin 11 to J25 pin 1"
    assert {n.name for n in j_screen[2].nets} == {"GND"}, (
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        cases.append((name, want, mutate))

    def _dup_gpio():
        GPIO["SW_STOP"] = GPIO["SW_UNDO"]

    def _ctrl_off_adc():
        # SWAP rather than collide -- setting CTRL to an already-used pin trips the
        # duplicate check first and never reaches the ADC assertion, which would
        # leave that gate unproven.
        GPIO["CTRL1_TIP"], GPIO["SW_RECPLAY"] = GPIO["SW_RECPLAY"], GPIO["CTRL1_TIP"]

    def _ring_order():
        # The other board reorders ITS connector and this one does not follow. The
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        text = text.replace("  (components\n", "  (components\n" + comp, 1)
        node = ('      (node\n        (ref "R99")\n        (pin "%s")\n'
                '        (pintype "PASSIVE"))\n')
        for _net, _pin in (("+5V_LED", "1"), ("LINK_TO_CONSOLE", "2")):
            _anchor = '(name "%s")\n      (class "Default")\n' % _net
            assert _anchor in text, (
                "ring_board.net's format or net names changed under _ring_pullup "
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        STATION_HEADERS["NOT_A_STATION"] = "J99"

    def _uart_split():
        # Swap LINK_TX with IND_DATA: GP18 is on no UART's TX set, and swapping
        # (not assigning) keeps every pin unique, so this reaches the UART gate
        # instead of the duplicate or expansion checks. No GPIO is spare on v3.
        GPIO["LINK_TX"], GPIO["IND_DATA"] = GPIO["IND_DATA"], GPIO["LINK_TX"]

    def _row_straddle():
        GPIO["LINK_TO_CONSOLE"], GPIO["IND_DATA"] = GPIO["IND_DATA"], GPIO["LINK_TO_CONSOLE"]

    def _exp_collide():
        GPIO["SW_STOP"] = EXPANSION_GPIO[0]

    def _ref_collision():
        # The renumbering failure PIN_REFS exists for, replayed literally: the
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
    def _screen_wrong_gpio():
        j_pi[11].disconnect()
        j_pi[12] += pi_gpio17

    # Each control names the gate it must trip. A control that trips some OTHER
    # gate proves nothing about its own and reads as a pass -- console_board_pcb.py
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    case("MIDI IN clamp diode reversed", "MIDI_CLAMP:", _clamp_reversed)
    case("reservoir electrolytic fitted backwards", "POLARITY:", _cap_backwards)
    case("link on a pin the NVMe board owns", "PI_RESERVED:", _reserved_pin)
    case("power button off GPIO3", "PWR_BTN:", _btn_pin)
    case("power button lead returned to GND", "PWR_BTN:", _btn_grounded)
    case("wrong footswitch count", "PIN_MAP:", _fsw_count)
    case("board terminates a station the panel lacks", "REAR_IO_COVER:", _station)
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                j_pi_btn[2] += pwr_btn_ret
            if mutate is _screen_wrong_gpio:
                j_pi[12].disconnect()
                j_pi[11] += pi_gpio17
            if mutate is _cap_backwards:
                _c30 = next(p for p in default_circuit.parts if p.ref == "C30")
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
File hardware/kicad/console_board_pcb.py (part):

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
    # right: the buffer, then the ribbon on the edge itself
    "U1":  (76.0, 44.0, 0),        # 74AHCT125, sat LOW on purpose. Its ring input is
                                   # pin 5; RING_DATA comes off the module's row A
                                   # (the bottom row), so with U1 up at y 34 that one
                                   # net had to climb 18 mm THROUGH the link / IND /
                                   # EXP / CTRL bundle that crosses the same gap, and
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    "R17": (96.9, 45.0, 90),       # 10k link_tx series, upright east of the
                                   # ribbon: 11 mm from J2 pin 21, 29 mm from
                                   # the Pico's GP16 pad
    "R18": (71.45, 63.0, 0),       # 6.8k link_rx; clears the PI PWR label at right
                                   # both legs within 28 mm
    "R16": (61.5, 59.6, 0),        # 100k ind_data pulldown, in the slim band
                                   # the same band: 22 mm from U1 pin 2; its GND
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# straight ordered row.
#
# v3 measured 1915 mm. The ~210 mm over v2 is the four CTRL sense nets (ring and
# presence, J20_REF/J21_REF/J20_RN/J21_RN and their GPIO ends): their series
# parts sit under the module, 50-60 mm from the jacks they serve, because the
# column beside U2 that would have put them under the jacks is the expansion
# header's. They are DC lines through 4.7k -- SLOW_SENSE_NETS, exempt from the
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# header's. The back is clear from the pads to R11/R21's pads, and it is the side a
# harness is continuity-checked against anyway.
PIN_LEGEND_REFS = ("J3", "J24")
PIN_LEGEND_NAME = {"+5V": "+5V", "GND": "GND", "IND_DATA_OUT": "DATA"}
PIN_LEGEND_GAP = 0.6     # pad copper edge to the text's near edge, mm


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    boxes += console_ring_power.stitch_keepouts(ORIGIN)
    n_vias = _stitch_gnd(board, fps, nets, netmap, boxes)
    n_vias += _stitch_grid(board, netmap[POUR_NET], fps, boxes)
    _route_screen_control(board, netmap["PI_GPIO17"])
    console_ring_power.install(board)

    # NOT pcbnew.ZONE_FILLER here: in-process it segfaults with no wxApp. The
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
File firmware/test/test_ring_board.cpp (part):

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  static const uint8_t cw[4] = {1, 0, 2, 3}, ccw[4] = {2, 0, 1, 3};
  for (int c = 0; c < (clicks < 0 ? -clicks : clicks); ++c) {
    for (const uint8_t state : clicks > 0 ? cw : ccw) {
      fake_arduino::digital[PIN_ENC_A] = state >> 1;
      fake_arduino::digital[PIN_ENC_B] = state & 1;
      encoderSample();
    }
  }
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  at(now += 20);
  assert(lastSnapshot(1) == start - 2);
  // A half click, reversed by contact bounce, counts nothing.
  fake_arduino::digital[PIN_ENC_A] = 0;
  encoderSample();
  fake_arduino::digital[PIN_ENC_A] = 1;
  encoderSample();
  at(now += 20);
  assert(lastSnapshot(1) == start - 2);
  // The button: an edge counts once it has held for 8 ms; odd means pressed.
  const uint32_t edges = lastSnapshot(2);
  fake_arduino::digital[PIN_ENC_SW] = LOW;
  at(now += 4);
  at(now += 10);
  at(now += 20);
  assert(lastSnapshot(2) == edges + 1);
  fake_arduino::digital[PIN_ENC_SW] = HIGH;
  at(now += 4);
  at(now += 10);
  at(now += 20);
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}

int main() {
  fake_arduino::digital[PIN_ENC_A] = fake_arduino::digital[PIN_ENC_B] = HIGH;
  fake_arduino::digital[PIN_ENC_SW] = HIGH;
  setup();
  cometProfile();
  cometOutput();
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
